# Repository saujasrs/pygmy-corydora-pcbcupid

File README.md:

# pygmy-corydora-pcbcupid
Pygmy Corydora Macropad Build at an event held by PCBCupid in Bangalore on May 18, 2026.
Built around the Glyph Mini RP2040.

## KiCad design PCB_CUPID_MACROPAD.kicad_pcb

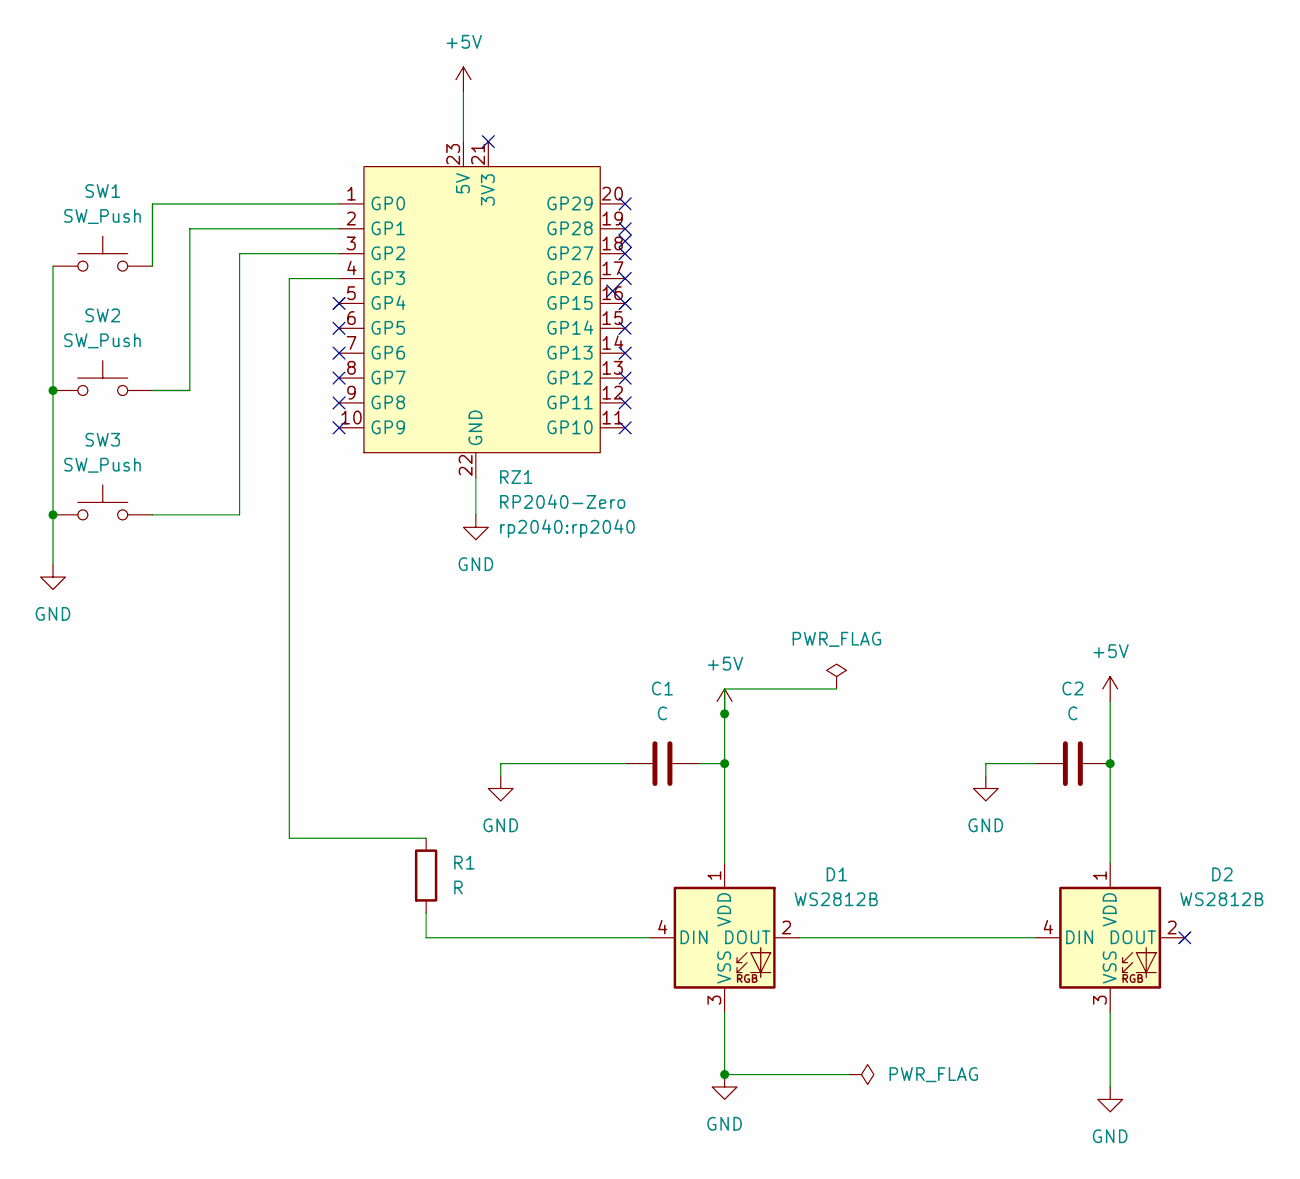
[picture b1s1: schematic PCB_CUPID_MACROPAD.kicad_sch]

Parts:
C1, C2: C; R_1206_3216Metric_Pad1.30x1.75mm_HandSolder
D1, D2: WS2812B; LED_WS2812B_PLCC4_5.0x5.0mm_P3.2mm
R1: R; R_0805_2012Metric_Pad1.20x1.40mm_HandSolder
RZ1: RP2040-Zero; rp2040
SW1, SW2, SW3: SW_Push; SW_Cherry_MX_1.00u_PCB

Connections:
+5V: C1.2, C2.2, D1.1 (VDD), D2.1 (VDD), RZ1.23 (5V)
GND: C1.1, C2.1, D1.3 (VSS), D2.3 (VSS), RZ1.22 (GND), SW1.1, SW2.1, SW3.1
unnamed: D1.4 (DIN), R1.2
unnamed: D1.2 (DOUT), D2.4 (DIN)
unnamed: RZ1.1 (GP0), SW1.2
unnamed: RZ1.2 (GP1), SW2.2
unnamed: RZ1.3 (GP2), SW3.2
unnamed: R1.1, RZ1.4 (GP3)

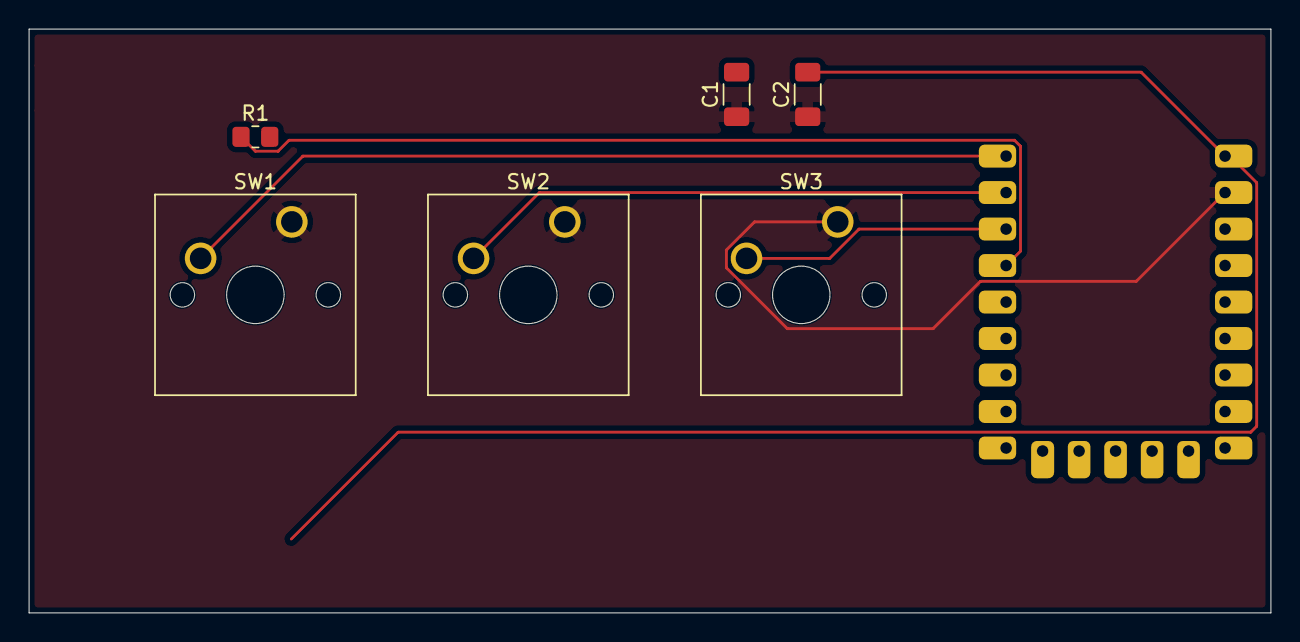
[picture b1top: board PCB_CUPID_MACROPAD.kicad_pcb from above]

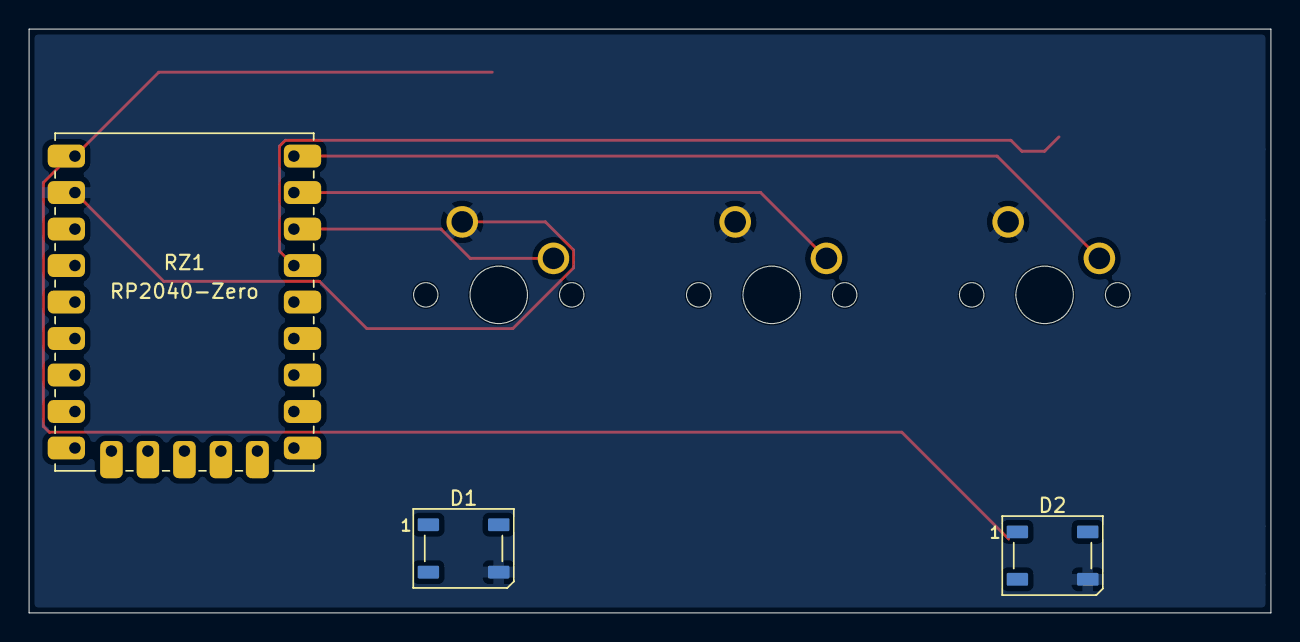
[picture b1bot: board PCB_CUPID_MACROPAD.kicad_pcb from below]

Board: 2 copper layers, 86.4 x 40.6 mm, 9 parts (3 on the bottom side), 8 nets.

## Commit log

2026-06-16 Enhance README with project details and image
    Added a description and image to the README.
